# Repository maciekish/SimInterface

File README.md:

SimInterface
============

Interfacing FSX and PMDG with Teensy USB hardware

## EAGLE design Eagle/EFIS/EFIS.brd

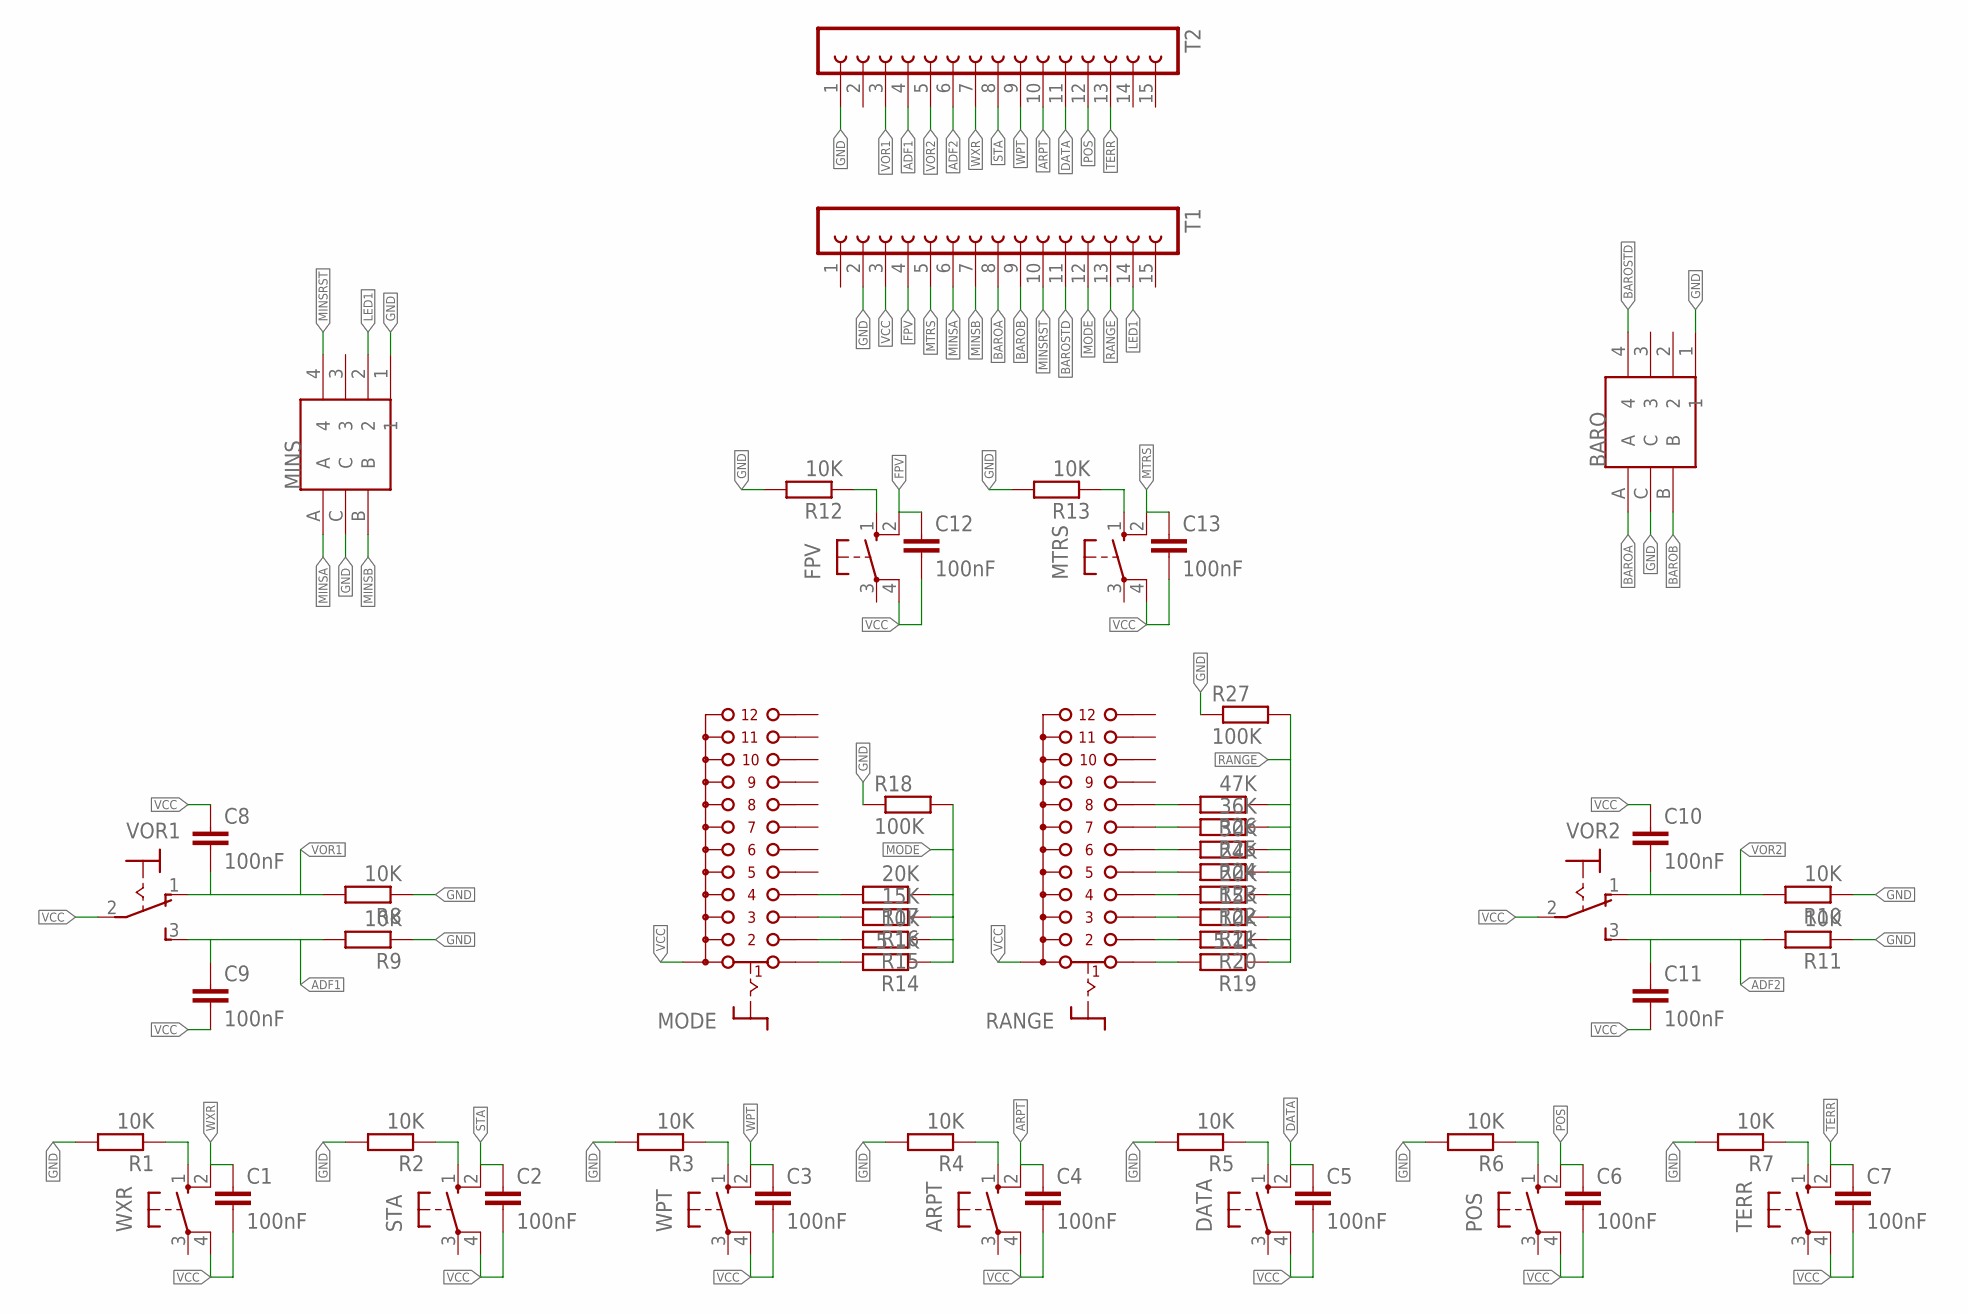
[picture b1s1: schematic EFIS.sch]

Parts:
ARPT: 10-XX; B3F-10XX
BARO: MERP12246GR; MERP1224126
C1, C2, C3, C4, C5, C6, C7, C8, C9, C10, C11, C12, C13: 100nF; C1206
DATA: 10-XX; B3F-10XX
FPV: 10-XX; B3F-10XX
MINS: MERP12246GR; MERP1224126
MODE: CK101X12
MTRS: 10-XX; B3F-10XX
POS: 10-XX; B3F-10XX
R1, R2, R3, R4, R5, R6, R7, R8, R9, R10, R11, R12, R13, R15, R20: 10K; R1206
R14, R19: 5.1K; R1206
R16, R21: 15K; R1206
R17, R22: 20K; R1206
R18, R27: 100K; R1206
R23: 24K; R1206
R24: 30K; R1206
R25: 36K; R1206
R26: 47K; R1206
RANGE: CK101X12
STA: 10-XX; B3F-10XX
T1, T2: FE15-1; FE15
TERR: 10-XX; B3F-10XX
VOR1, VOR2: 320-916
WPT: 10-XX; B3F-10XX
WXR: 10-XX; B3F-10XX

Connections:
ADF1: C9.1, R9.2, T2.4, VOR1.3 (S)
ADF2: C11.1, R11.2, T2.6, VOR2.3 (S)
ARPT: ARPT.2 (S1), C4.1, T2.10
BAROA: BARO.A, T1.8
BAROB: BARO.B, T1.9
BAROSTD: BARO.4, T1.11
DATA: C5.1, DATA.2 (S1), T2.11
FPV: C12.1, FPV.2 (S1), T1.4
GND: BARO.1, BARO.C, MINS.1, MINS.C, R1.2, R2.2, R3.2, R4.2, R5.2, R6.2, R7.2, R8.1, R9.1, R10.1, R11.1, R12.2, R13.2, R18.1, R27.1, T1.2, T2.1
LED1: MINS.2, T1.14
MINSA: MINS.A, T1.6
MINSB: MINS.B, T1.7
MINSRST: MINS.4, T1.10
MODE: R14.1, R15.1, R16.1, R17.1, R18.2, T1.12
MTRS: C13.1, MTRS.2 (S1), T1.5
unnamed: R1.1, WXR.1 (S)
unnamed: R2.1, STA.1 (S)
unnamed: R3.1, WPT.1 (S)
unnamed: ARPT.1 (S), R4.1
unnamed: DATA.1 (S), R5.1
unnamed: POS.1 (S), R6.1
unnamed: R7.1, TERR.1 (S)
unnamed: FPV.1 (S), R12.1
unnamed: MTRS.1 (S), R13.1
unnamed: MODE.1, R14.2
unnamed: MODE.2, R15.2
unnamed: MODE.3, R16.2
unnamed: MODE.4, R17.2
unnamed: R19.2, RANGE.1
unnamed: R20.2, RANGE.2
unnamed: R21.2, RANGE.3
unnamed: R22.2, RANGE.4
unnamed: R23.2, RANGE.5
unnamed: R24.2, RANGE.6
unnamed: R25.2, RANGE.7
unnamed: R26.2, RANGE.8
POS: C6.1, POS.2 (S1), T2.12
RANGE: R19.1, R20.1, R21.1, R22.1, R23.1, R24.1, R25.1, R26.1, R27.2, T1.13
STA: C2.1, STA.2 (S1), T2.8
TERR: C7.1, T2.13, TERR.2 (S1)
VCC: ARPT.4 (P1), C1.2, C2.2, C3.2, C4.2, C5.2, C6.2, C7.2, C8.1, C9.2, C10.1, C11.2, C12.2, C13.2, DATA.4 (P1), FPV.4 (P1), MODE.A, MTRS.4 (P1), POS.4 (P1), RANGE.A, STA.4 (P1), T1.3, TERR.4 (P1), VOR1.2, VOR2.2, WPT.4 (P1), WXR.4 (P1)
VOR1: C8.2, R8.2, T2.3, VOR1.1 (O)
VOR2: C10.2, R10.2, T2.5, VOR2.1 (O)
WPT: C3.1, T2.9, WPT.2 (S1)
WXR: C1.1, T2.7, WXR.2 (S1)

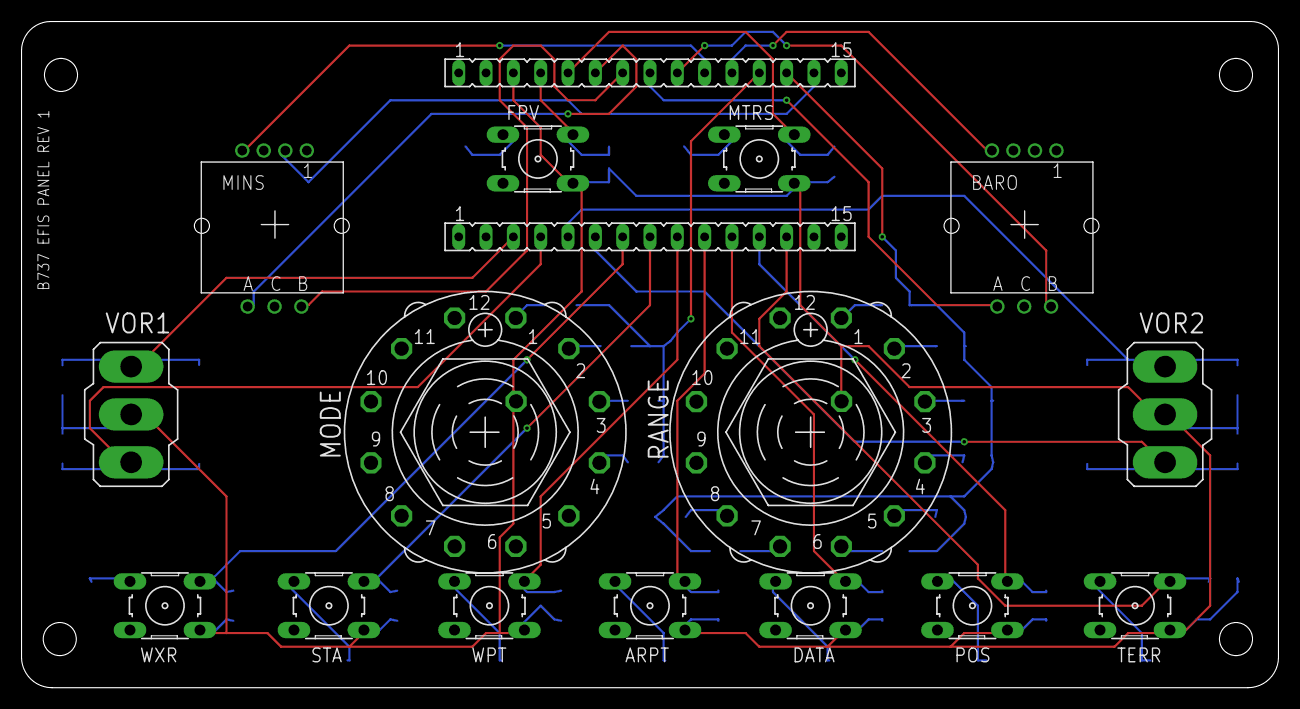
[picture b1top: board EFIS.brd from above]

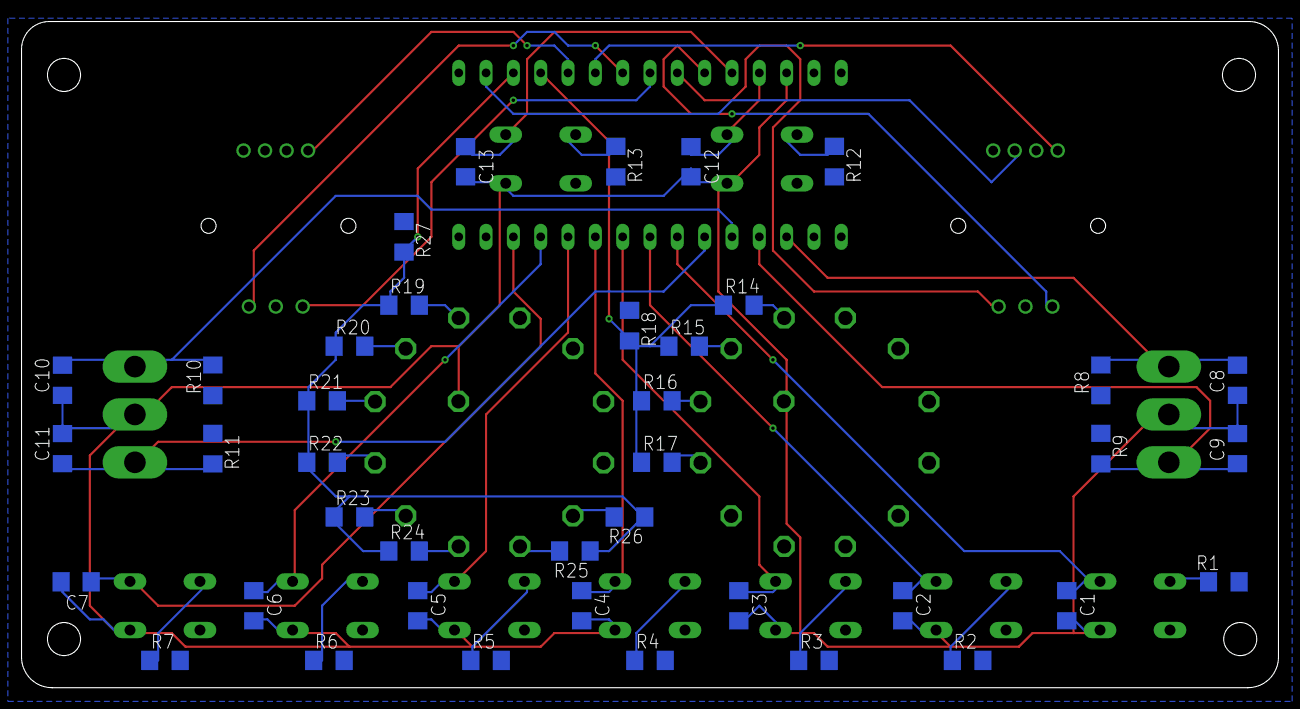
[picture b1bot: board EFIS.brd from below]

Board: 2 copper layers, 116.8 x 61.9 mm, 57 parts (40 on the bottom side), 45 nets.

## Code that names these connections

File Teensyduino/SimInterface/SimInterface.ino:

#include <Encoder.h>
#include <Queue.h>

#define POS_1 888
#define POS_2 931
#define POS_3 971
int current_pos = 0;

// Pins
#define VOR1   1
#define ADF1   2
#define VOR2   3
#define ADF2   4
#define WXR    5
#define STA    6
#define WPT    7
#define ARPT   8
#define DATA   9
#define POS    10
#define TERR   11
#define LED    13
#define RANGE  14
#define MODE   15
#define BAROSTD 16
#define MINSRST 17
#define BAROB  18
#define BAROA  19
#define MINSB  20
#define MINSA  21
#define MTRS   22
#define FPV    23

Queue sendQueue;
int n;

Encoder baro(18, 19);
    
void setup() {
  Serial.begin(9600);
  Serial.println(F("SimInterface Initialized"));
  
  //Setup pins
  for (int i=0; i<=23; i++) {
    pinMode(i, INPUT);
  }
  pinMode(LED, OUTPUT);
  
  //Attach interrupts
  attachInterrupt(0, pin0, RISING);
  attachInterrupt(1, pin1, RISING);
  attachInterrupt(2, pin2, RISING);
  attachInterrupt(3, pin3, RISING);
  attachInterrupt(4, pin4, RISING);
  attachInterrupt(5, pin5, RISING);
  attachInterrupt(6, pin6, RISING);
  attachInterrupt(7, pin7, RISING);
  attachInterrupt(8, pin8, RISING);
  attachInterrupt(9, pin9, RISING);
  attachInterrupt(10, pin10, RISING);
  attachInterrupt(11, pin11, RISING);
  attachInterrupt(12, pin12, RISING);
  attachInterrupt(13, pin13, RISING);
  attachInterrupt(14, pin14, RISING);
  attachInterrupt(15, pin15, RISING);
  attachInterrupt(16, pin16, RISING);
  attachInterrupt(17, pin17, RISING);
  attachInterrupt(18, pin18, RISING);
  attachInterrupt(19, pin19, RISING);
  attachInterrupt(20, pin20, RISING);
  attachInterrupt(21, pin21, RISING);
  attachInterrupt(22, pin22, RISING);
  attachInterrupt(23, pin23, RISING);
  
  //Special extra interrupts for disabling VOR1, ADF1, VOR2, ADF2
  attachInterrupt(0, pin0off, RISING);
  attachInterrupt(1, pin1off, RISING);
  attachInterrupt(2, pin2off, RISING);
  attachInterrupt(3, pin3off, RISING);
  
  //Blink LED to indicate we are alive
  digitalWrite(LED, HIGH);
  delay(100);
  digitalWrite(LED, LOW);
}

// RawHID packets are always 64 bytes
byte buffer[64];
byte receiveBuffer[64];
unsigned int packetCount = 0;

void loop() {
  delay(50);
  
  sendQueue.Run(millis());
  
  /*n = RawHID.recv(receiveBuffer, 1); // 0 timeout = do not wait
  if (n > 0) {
    //String message = String((char *)buffer);
    //Serial.println(message);
    
    digitalWrite(10, receiveBuffer[1]);
    digitalWrite(11, receiveBuffer[2]);
    digitalWrite(12, receiveBuffer[3]);
    digitalWrite(15, receiveBuffer[4]);
    digitalWrite(16, receiveBuffer[5]);
    digitalWrite(17, receiveBuffer[6]);
    
        
    byte chars[63];
    memcpy(chars, receiveBuffer, 63);
    
    String command = String("");
    for (int i=1; i<63; i++) {
      Serial.print((char)receiveBuffer[i]);
      //command += String((char)receiveBuffer[i]);
      //Serial.print(String((char)receiveBuffer[i]));
    }
    Serial.println(command);
        
    // the computer sent a message.  Display the bits
    // of the first byte on pin 0 to 7.  Ignore the
    // other 63 bytes!
    Serial.print(F("Received packet, first byte: "));
    Serial.println((int)buffer[0]);
    for (int i=0; i<8; i++) {
      int b = buffer[0] & (1 << i);
      digitalWrite(i, b);
    }
  }*/
}

void pin0() {
  buttonHandler(0);
}

void pin1() {
  buttonHandler(1);
}

void pin2() {
  buttonHandler(2);
}

void pin3() {
  buttonHandler(3);
}

void pin4() {
  buttonHandler(4);
}

void pin5() {
  buttonHandler(5);
}

void pin6() {
  buttonHandler(6);
}

void pin7() {
  buttonHandler(7);
}

void pin8() {
  buttonHandler(8);
}

void pin9() {
  buttonHandler(9);
}

void pin10() {
  buttonHandler(10);
}

void pin11() {
  buttonHandler(11);
}

void pin12() {
  buttonHandler(12);
}

void pin13() {
  buttonHandler(13);
}

void pin14() {
  buttonHandler(14);
}

void pin15() {
  buttonHandler(15);
}

void pin16() {
  buttonHandler(16);
}

void pin17() {
  buttonHandler(17);
}

void pin18() {
  buttonHandler(18);
}

void pin19() {
  buttonHandler(19);
}

void pin20() {
  buttonHandler(20);
}

void pin21() {
  buttonHandler(21);
}

void pin22() {
  buttonHandler(22);
}

void pin23() {
  buttonHandler(23);
}

void pin0off() {
  buttonHandler(0 + 128);
}

void pin1off() {
  buttonHandler(1 + 128);
}

void pin2off() {
  buttonHandler(2 + 128);
}

void pin3off() {
  buttonHandler(3 + 128);
}

boolean bounced() {
  static unsigned long last_interrupt_time = 0;
  unsigned long interrupt_time = millis();
  if (interrupt_time - last_interrupt_time < 250) {
    last_interrupt_time = interrupt_time;
    return true;
  } else {
    last_interrupt_time = interrupt_time;
    return false;
  }
}

void buttonHandler(int button) {
  if (!bounced()) {
    Serial.print("Pressed ");
    Serial.println(button);
    
    String message = "EFIS.L:"; //Left EFIS
    
    switch(button) {
      //VOR & ADF
      case VOR1:
        message = message + "VOR1";
        break;
      case VOR1 + 128:
        message = message + "VOR1.ADF1.OFF";
        break;
      case ADF1:
        message = message + "ADF1";
        break;
      case ADF1 + 128:
        message = message + "VOR1.ADF1.OFF";
        break;
      case VOR2:
        message = message + "VOR2";
        break;
      case VOR2 + 128:
        message = message + "VOR2.ADF1.OFF";
        break;
      case ADF2:
        message = message + "ADF2";
        break;
      case ADF2 + 128:
        message = message + "VOR2.ADF1.OFF";
        break;
      //Buttons
      case WXR:
        message = message + "WXR";
        break;
      case STA:
        message = message + "STA";
        break;
      case WPT:
        message = message + "WPT";
        break;
      case ARPT:
        message = message + "ARPT";
        break;
      case DATA:
        message = message + "DATA";
        break;
      case POS:
        message = message + "POS";
        break;
      case TERR:
        message = message + "TERR";
        break;
      case BAROSTD:
        message = message + "BAROSTD";
        break;
      case MINSRST:
        message = message + "MINSRST";
        break;
      case MTRS:
        message = message + "MTRS";
        break;
      case FPV:
        message = message + "FPV";
        break;
    }
    
    message.getBytes(buffer, 64);
    RawHID.send(buffer, 100);
    
    //Blink LED
    digitalWrite(LED, HIGH);
    delay(2);
    digitalWrite(LED, LOW);
  }
}

int sendData(unsigned long now)
{
    // first 2 bytes are a signature
    buffer[0] = 0x73;
    buffer[1] = 0x70;
    // next 24 bytes are analog measurements
    for (int i=0; i<12; i++) {
      int val = analogRead(i);
      buffer[i * 2 + 2] = highByte(val);
      buffer[i * 2 + 3] = lowByte(val);
    }
    // fill the rest with zeros
    for (int i=26; i<62; i++) {
      buffer[i] = 0;
    }
    // and put a count of packets sent at the end
    buffer[62] = highByte(packetCount);
    buffer[63] = lowByte(packetCount);
    // actually send the packet
    n = RawHID.send(buffer, 100);
    if (n > 0) {
      Serial.print(F("Transmit packet "));
      Serial.println(packetCount);
      packetCount = packetCount + 1;
    } else {
      Serial.println(F("Unable to transmit packet"));
    }
}

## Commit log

2014-03-07 Added a basic FSX project. Doesnt work with PMDG though.
2014-03-08 Added full control of the PMDG NGX EFIS panel
2014-03-08 Added MCP buttons
2014-03-08 Added all MCP controls and changed radiobuttons to checkboxes
2014-03-08 Reorganized folder structure
2014-03-08 Prepared Teensyduino project with scheduling
2014-03-08 Basic two way communication proof of concept. Needs big time refactoring etc.
2014-03-13 Added an Eagle project
2014-03-13 Initial board layout
2014-03-14 Button connections in Eagle
2014-03-16 All components placed and some manual routing
2014-03-16 REV 1 PCB
2014-11-06 Updated sketch
2014-11-08 Working
2014-11-08 More functionality
